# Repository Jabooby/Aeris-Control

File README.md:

# AERISCONTROL
Autonomous sail boat with a multiaxial sail control

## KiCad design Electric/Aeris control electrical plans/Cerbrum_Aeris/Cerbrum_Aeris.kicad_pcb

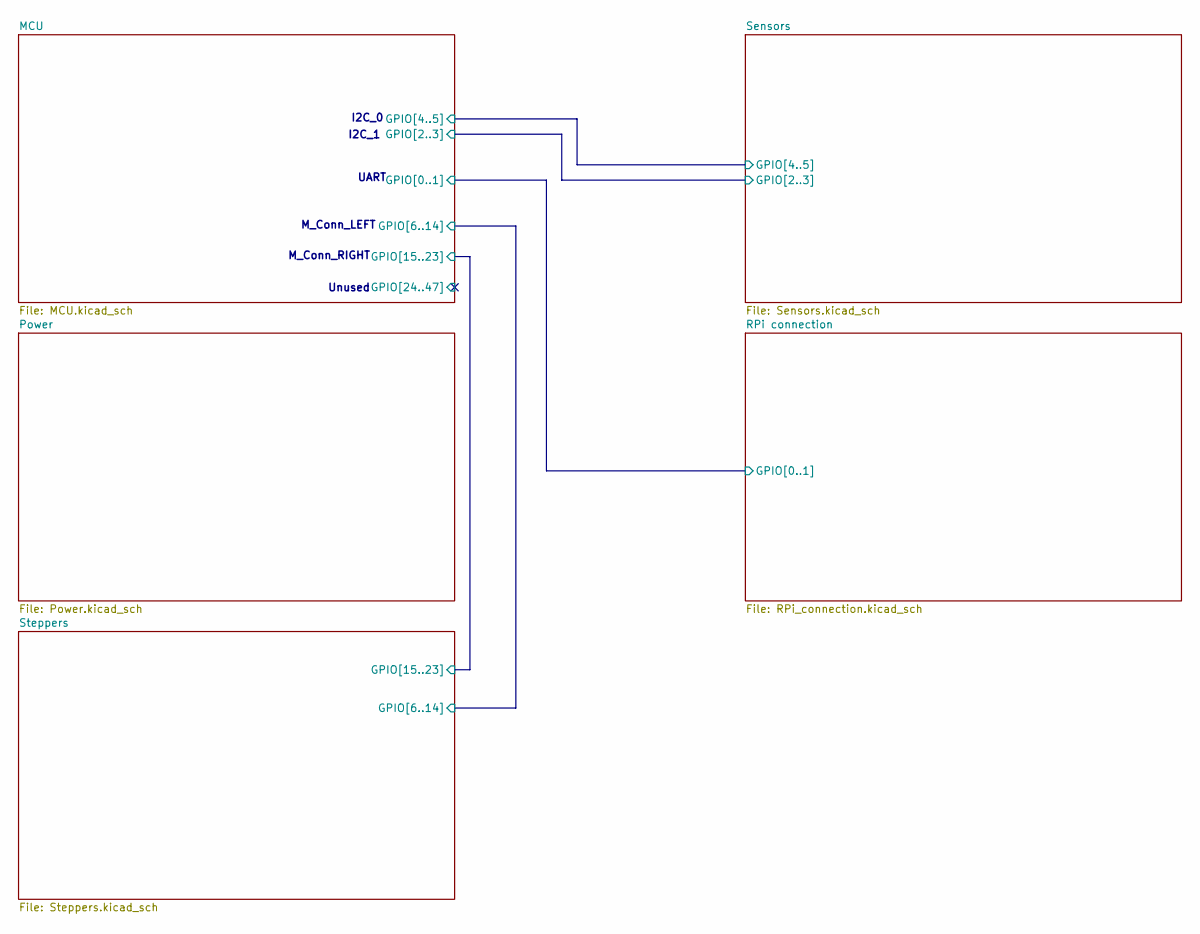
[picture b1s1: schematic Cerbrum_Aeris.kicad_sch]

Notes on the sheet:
Unused
I2C_1
M_Conn_RIGHT
I2C_0
UART
M_Conn_LEFT

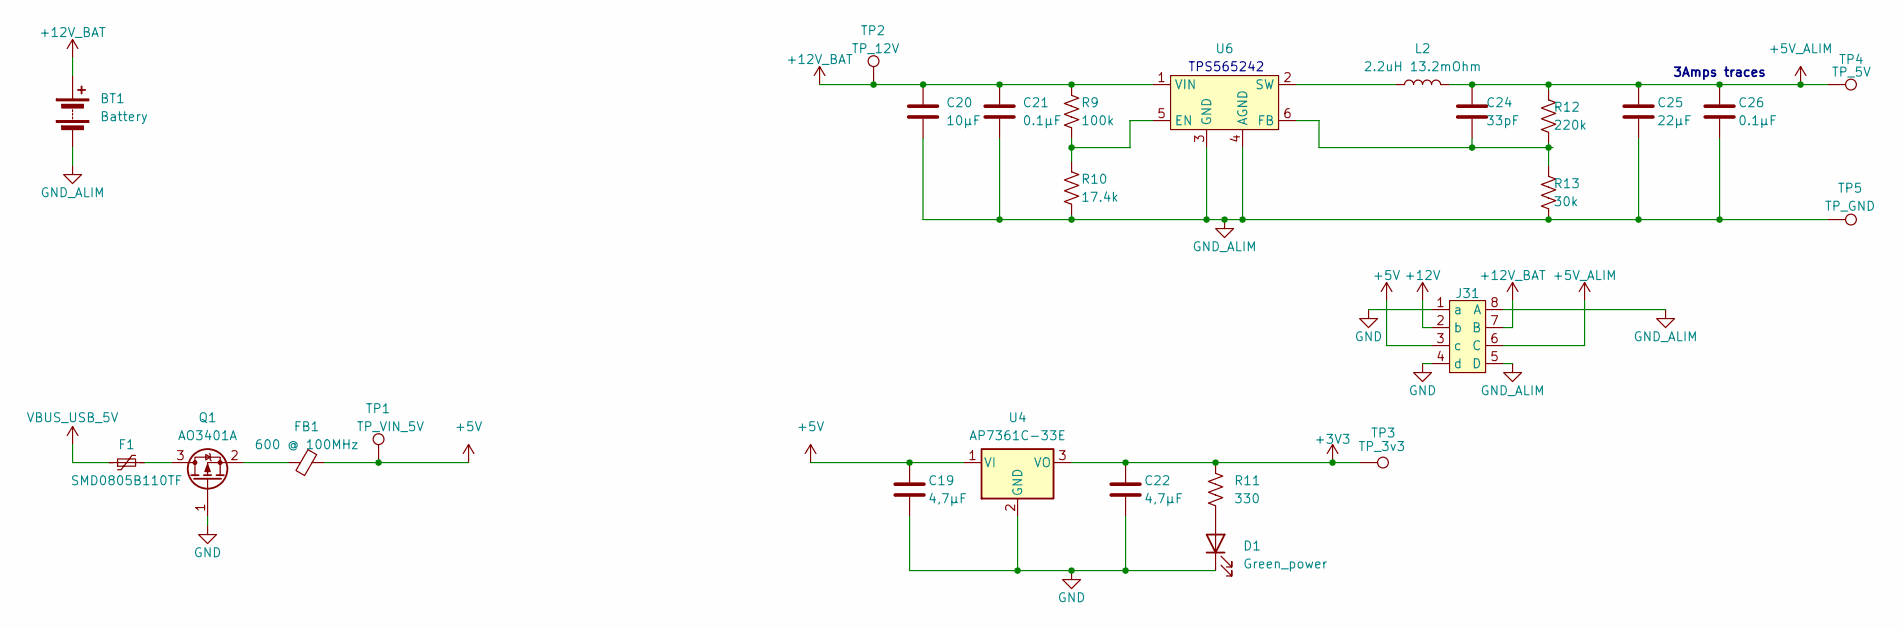
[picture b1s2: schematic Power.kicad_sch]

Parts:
BT1: Battery; TerminalBlock_Altech_AK300-2_P5.00mm
C19, C22: 4,7µF; C_0805_2012Metric_Pad1.18x1.45mm_HandSolder
C20: 10µF; C_0805_2012Metric_Pad1.18x1.45mm_HandSolder
C21, C26: 0.1µF; C_0603_1608Metric_Pad1.08x0.95mm_HandSolder
C24: 33pF; C_0603_1608Metric_Pad1.08x0.95mm_HandSolder
C25: 22µF; C_0805_2012Metric_Pad1.18x1.45mm_HandSolder
D1: Green_power; D_0805_2012Metric
F1: SMD0805B110TF; Fuse_0805_2012Metric
FB1: 600 @ 100MHz; R_0805_2012Metric_Pad1.20x1.40mm_HandSolder
J31: SJ_Stepper_1-5mm
L2: 2.2uH 13.2mOhm; L_TDK_VLP8040
Q1: AO3401A; SOT-23
R9: 100k; R_0603_1608Metric_Pad0.98x0.95mm_HandSolder
R10: 17.4k; R_0603_1608Metric_Pad0.98x0.95mm_HandSolder
R11: 330; R_0603_1608Metric_Pad0.98x0.95mm_HandSolder
R12: 220k; R_0603_1608Metric_Pad0.98x0.95mm_HandSolder
R13: 30k; R_0603_1608Metric_Pad0.98x0.95mm_HandSolder
TP1: TP_VIN_5V; TestPoint_Pad_D1.0mm
TP2: TP_12V; TestPoint_Pad_D1.0mm
TP3: TP_3v3; TestPoint_Pad_D1.0mm
TP4: TP_5V; TestPoint_Pad_D1.0mm
TP5: TP_GND; TestPoint_Pad_1.0x1.0mm
U4: AP7361C-33E; SOT-223-3_TabPin2
U6: SOT-563

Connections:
+3V3: C22.2, R11.1, TP3.1, U4.3 (VO); also elsewhere on the board
+5V: C19.2, FB1.2, J31.3 (c), TP1.1, U4.1 (VI); also elsewhere on the board
+5V_ALIM: C24.1, C25.1, C26.1, J31.6 (C), L2.2, R12.1, TP4.1; also elsewhere on the board
+12V: J31.2 (b); also elsewhere on the board
+12V_BAT: BT1.1 (+), C20.1, C21.1, J31.7 (B), R9.1, TP2.1, U6.1 (VIN); also elsewhere on the board
GND: C19.1, C22.1, D1.1 (K), J31.1 (a), J31.4 (d), Q1.1 (G), U4.2 (GND); also elsewhere on the board
GND_ALIM: BT1.2 (-), C20.2, C21.2, C25.2, C26.2, J31.5 (D), J31.8 (A), R10.2, R13.2, TP5.1, U6.3 (GND), U6.4 (AGND); also elsewhere on the board
unnamed: D1.2 (A), R11.2
unnamed: F1.2, Q1.3 (D)
unnamed: FB1.1, Q1.2 (S)
unnamed: R9.2, R10.1, U6.5 (EN)
unnamed: C24.2, R12.2, R13.1, U6.6 (FB)
unnamed: L2.1, U6.2 (SW)
VBUS_USB_5V: F1.1; also elsewhere on the board

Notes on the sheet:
TPS565242
3Amps traces

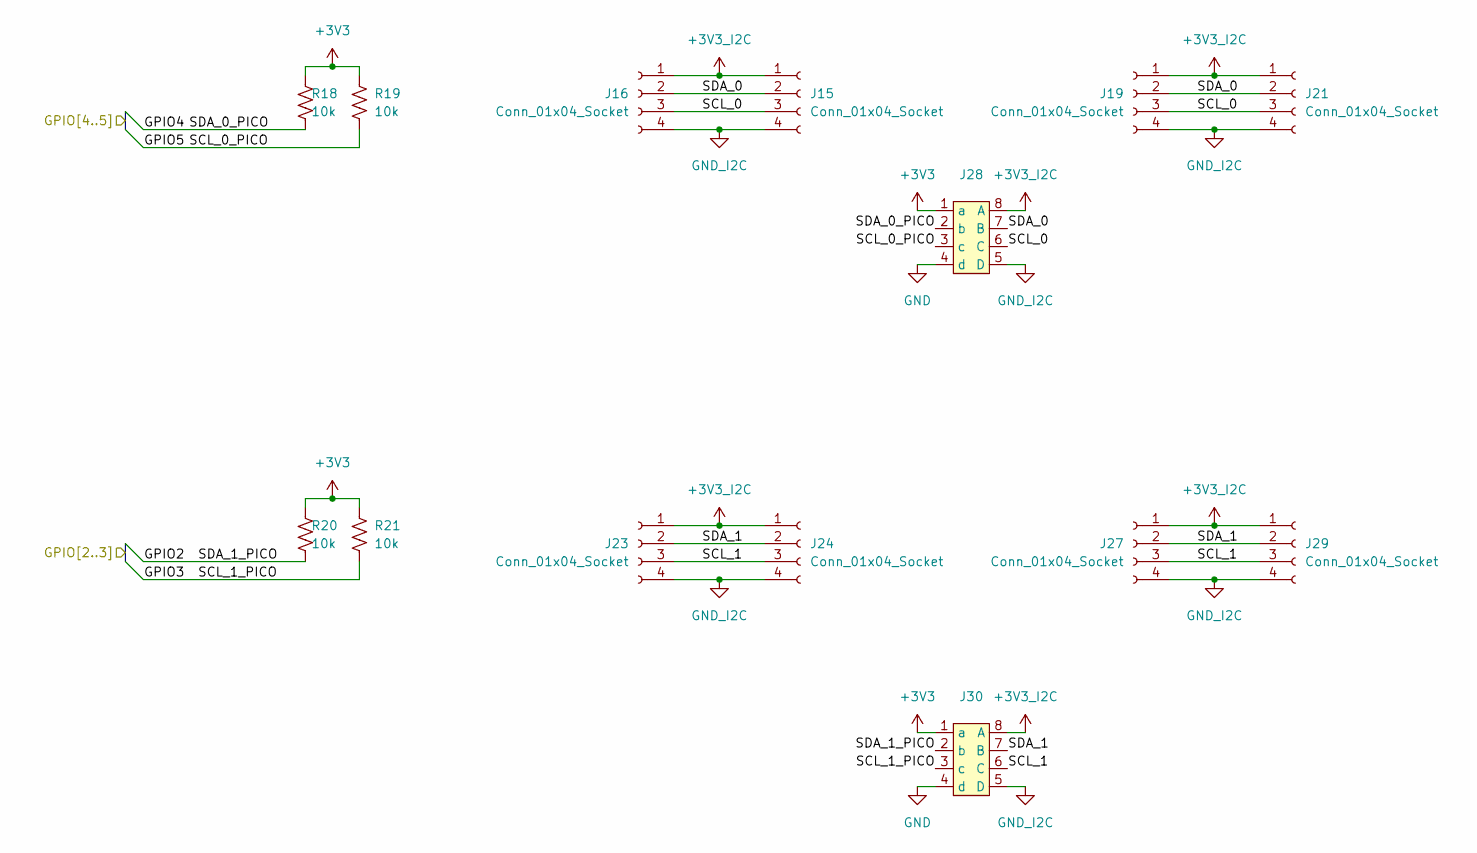
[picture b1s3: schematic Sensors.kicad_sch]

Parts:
J15, J16, J19, J21, J23, J24, J27, J29: Conn_01x04_Socket; PinSocket_1x04_P2.54mm_Vertical
J28, J30: SJ_Stepper_1-5mm
R18, R19, R20, R21: 10k; R_0603_1608Metric

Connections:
+3V3: J28.1 (a), J30.1 (a), R18.1, R19.1, R20.1, R21.1; also elsewhere on the board
+3V3_I2C: J15.1, J16.1, J19.1, J21.1, J23.1, J24.1, J27.1, J28.8 (A), J29.1, J30.8 (A)
/MCU/GPIO2: J30.2 (b), R20.2; also elsewhere on the board
/MCU/GPIO3: J30.3 (c), R21.2; also elsewhere on the board
/MCU/GPIO4: J28.2 (b), R18.2; also elsewhere on the board
/MCU/GPIO5: J28.3 (c), R19.2; also elsewhere on the board
/Sensors/SCL_0: J15.3, J16.3, J19.3, J21.3, J28.6 (C)
/Sensors/SCL_1: J23.3, J24.3, J27.3, J29.3, J30.6 (C)
/Sensors/SDA_0: J15.2, J16.2, J19.2, J21.2, J28.7 (B)
/Sensors/SDA_1: J23.2, J24.2, J27.2, J29.2, J30.7 (B)
GND: J28.4 (d), J30.4 (d); also elsewhere on the board
GND_I2C: J15.4, J16.4, J19.4, J21.4, J23.4, J24.4, J27.4, J28.5 (D), J29.4, J30.5 (D)

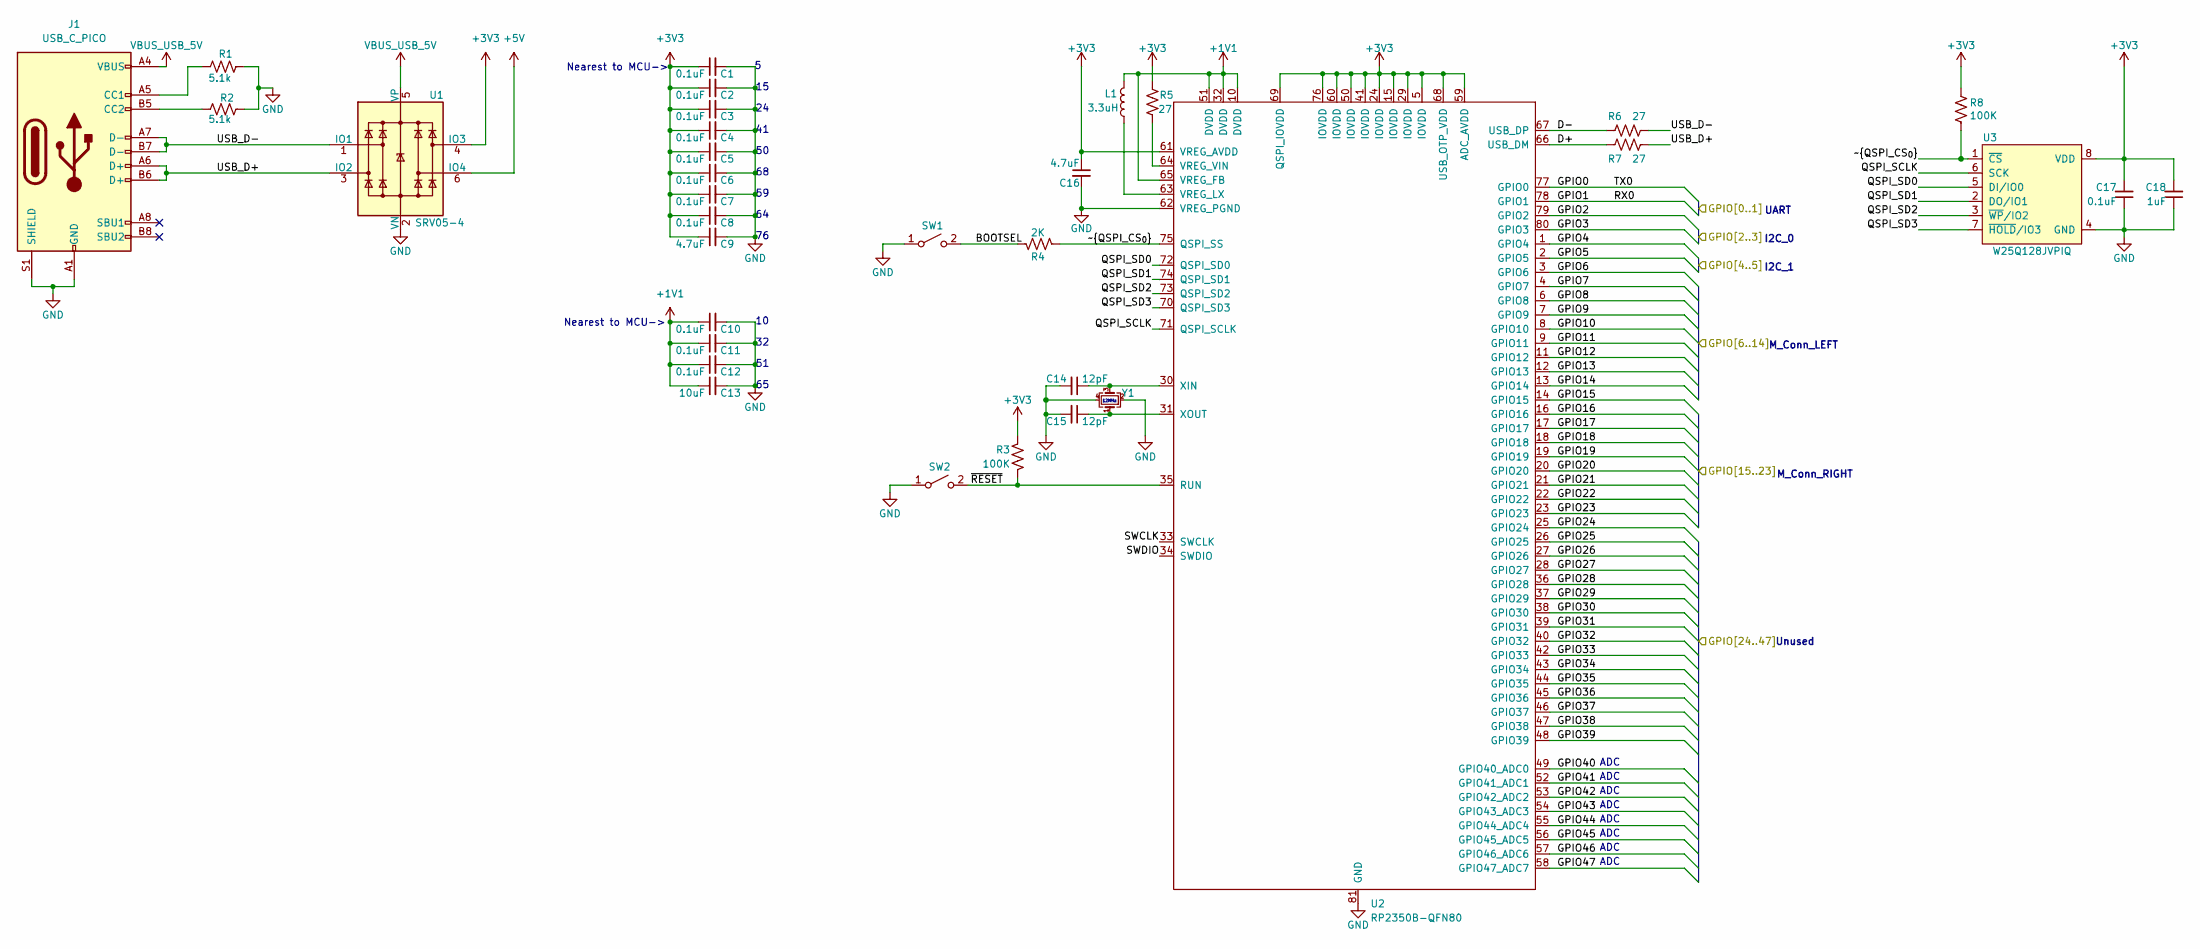
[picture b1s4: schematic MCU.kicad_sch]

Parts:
C1, C2, C3, C4, C5, C6, C7, C8, C10, C11, C12, C17: 0.1uF; C_0603_1608Metric
C9, C16: 4.7uF; C_0603_1608Metric
C13: 10uF; C_0603_1608Metric
C14, C15: 12pF; C_0603_1608Metric
C18: 1uF; C_0603_1608Metric
J1: USB_C_PICO; USB_C_Receptacle_G-Switch_GT-USB-7010ASV
L1: 3.3uH; R_0805_2012Metric
R1, R2: 5.1k; R_0603_1608Metric_Pad0.98x0.95mm_HandSolder
R3, R8: 100K; R_0603_1608Metric
R4: 2K; R_0603_1608Metric
R5, R6, R7: 27; R_0603_1608Metric
SW1: SW_BOOTSEL; SW_SPST_B3U-1000P; LCSC C561514
SW2: SW_RESET; SW_SPST_B3U-1000P; LCSC C561514
U1: SRV05-4; SOT-23-6
U2: RP2350B-QFN80; QFN-80-1EP_10x10mm_P0.4mm_EP3.4x3.4mm_ThermalVias
U3: W25Q128JVPIQ; WSON-8-1EP_6x5mm_P1.27mm_EP3.4x4mm; LCSC C190862
Y1: CM4012M00012001; Crystal_SMD_2520-4Pin_2.5x2.0mm; LCSC C7294611

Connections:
+1V1: C10.1, C11.1, C12.1, C13.1, L1.2, U2.10 (DVDD), U2.32 (DVDD), U2.51 (DVDD), U2.65 (VREG_FB)
+3V3: C1.1, C2.1, C3.1, C4.1, C5.1, C6.1, C7.1, C8.1, C9.1, C16.1, C17.2, C18.2, R3.1, R5.1, R8.2, U1.4 (IO3), U2.5 (IOVDD), U2.15 (IOVDD), U2.24 (IOVDD), U2.29 (IOVDD), U2.41 (IOVDD), U2.50 (IOVDD), U2.59 (ADC_AVDD), U2.60 (IOVDD), U2.61 (VREG_AVDD), U2.68 (USB_OTP_VDD), U2.69 (QSPI_IOVDD), U2.76 (IOVDD), U3.8 (VDD); also elsewhere on the board
+5V: U1.6 (IO4); also elsewhere on the board
/MCU/BOOTSEL: R4.2, SW1.2 (B); also elsewhere on the board
/MCU/D+: R7.2, U2.66 (USB_DM)
/MCU/D-: R6.1, U2.67 (USB_DP)
/MCU/GPIO0: U2.77 (GPIO0); also elsewhere on the board
/MCU/GPIO1: U2.78 (GPIO1); also elsewhere on the board
/MCU/GPIO2: U2.79 (GPIO2); also elsewhere on the board
/MCU/GPIO3: U2.80 (GPIO3); also elsewhere on the board
/MCU/GPIO4: U2.1 (GPIO4); also elsewhere on the board
/MCU/GPIO5: U2.2 (GPIO5); also elsewhere on the board
/MCU/GPIO6: U2.3 (GPIO6); also elsewhere on the board
/MCU/GPIO7: U2.4 (GPIO7); also elsewhere on the board
/MCU/GPIO8: U2.6 (GPIO8); also elsewhere on the board
/MCU/GPIO9: U2.7 (GPIO9); also elsewhere on the board
/MCU/GPIO10: U2.8 (GPIO10); also elsewhere on the board
/MCU/GPIO11: U2.9 (GPIO11); also elsewhere on the board
/MCU/GPIO12: U2.11 (GPIO12); also elsewhere on the board
/MCU/GPIO13: U2.12 (GPIO13); also elsewhere on the board
/MCU/GPIO14: U2.13 (GPIO14); also elsewhere on the board
/MCU/GPIO15: U2.14 (GPIO15); also elsewhere on the board
/MCU/GPIO16: U2.16 (GPIO16); also elsewhere on the board
/MCU/GPIO17: U2.17 (GPIO17); also elsewhere on the board
/MCU/GPIO18: U2.18 (GPIO18); also elsewhere on the board
/MCU/GPIO19: U2.19 (GPIO19); also elsewhere on the board
/MCU/GPIO20: U2.20 (GPIO20); also elsewhere on the board
/MCU/GPIO21: U2.21 (GPIO21); also elsewhere on the board
/MCU/GPIO22: U2.22 (GPIO22); also elsewhere on the board
/MCU/GPIO23: U2.23 (GPIO23); also elsewhere on the board
/MCU/GPIO24: U2.25 (GPIO24)
/MCU/GPIO25: U2.26 (GPIO25)
/MCU/GPIO26: U2.27 (GPIO26)
/MCU/GPIO27: U2.28 (GPIO27)
/MCU/GPIO28: U2.36 (GPIO28)
/MCU/GPIO29: U2.37 (GPIO29)
/MCU/GPIO30: U2.38 (GPIO30)
/MCU/GPIO31: U2.39 (GPIO31)
/MCU/GPIO32: U2.40 (GPIO32)
/MCU/GPIO33: U2.42 (GPIO33)
/MCU/GPIO34: U2.43 (GPIO34)
/MCU/GPIO35: U2.44 (GPIO35)
/MCU/GPIO36: U2.45 (GPIO36)
/MCU/GPIO37: U2.46 (GPIO37)
/MCU/GPIO38: U2.47 (GPIO38)
/MCU/GPIO39: U2.48 (GPIO39)
/MCU/GPIO40: U2.49 (GPIO40_ADC0)
/MCU/GPIO41: U2.52 (GPIO41_ADC1)
/MCU/GPIO42: U2.53 (GPIO42_ADC2)
/MCU/GPIO43: U2.54 (GPIO43_ADC3)
/MCU/GPIO44: U2.55 (GPIO44_ADC4)
/MCU/GPIO45: U2.56 (GPIO45_ADC5)
/MCU/GPIO46: U2.57 (GPIO46_ADC6)
/MCU/GPIO47: U2.58 (GPIO47_ADC7)
/MCU/QSPI_SCLK: U2.71 (QSPI_SCLK), U3.6 (SCK)
/MCU/QSPI_SD0: U2.72 (QSPI_SD0), U3.5 (DI/IO0)
/MCU/QSPI_SD1: U2.74 (QSPI_SD1), U3.2 (DO/IO1)
/MCU/QSPI_SD2: U2.73 (QSPI_SD2), U3.3 (~WP/IO2)
/MCU/QSPI_SD3: U2.70 (QSPI_SD3), U3.7 (~HOLD/IO3)
/MCU/SWCLK: U2.33 (SWCLK)
/MCU/SWDIO: U2.34 (SWDIO)
/MCU/USB_D+: J1.A6 (D+), J1.B6 (D+), R7.1, U1.3 (IO2)
/MCU/USB_D-: J1.A7 (D-), J1.B7 (D-), R6.2, U1.1 (IO1)
/MCU/~QSPI_CS_{0}: R4.1, R8.1, U2.75 (QSPI_SS), U3.1 (~CS)
/MCU/~RESET: R3.2, SW2.2 (B), U2.35 (RUN); also elsewhere on the board
GND: C1.2, C2.2, C3.2, C4.2, C5.2, C6.2, C7.2, C8.2, C9.2, C10.2, C11.2, C12.2, C13.2, C14.2, C15.2, C16.2, C17.1, C18.1, J1.A1 (GND), J1.A12 (GND), J1.B1 (GND), J1.B12 (GND), J1.S1 (SHIELD), R1.2, R2.2, SW1.1 (A), SW2.1 (A), U1.2 (VN), U2.62 (VREG_PGND), U2.81 (GND), U3.4 (GND), U3.9 (GND), Y1.2, Y1.4; also elsewhere on the board
unnamed: J1.A5 (CC1), R1.1
unnamed: J1.B5 (CC2), R2.1
unnamed: L1.1, U2.63 (VREG_LX)
unnamed: R5.2, U2.64 (VREG_VIN)
unnamed: C14.1, U2.30 (XIN), Y1.3
unnamed: C15.1, U2.31 (XOUT), Y1.1
VBUS_USB_5V: J1.A4 (VBUS), J1.A9 (VBUS), J1.B4 (VBUS), J1.B9 (VBUS), U1.5 (VP); also elsewhere on the board

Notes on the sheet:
Nearest to MCU->
M_Conn_LEFT
ADC
Unused
I2C_0
M_Conn_RIGHT
12MHz
I2C_1
UART

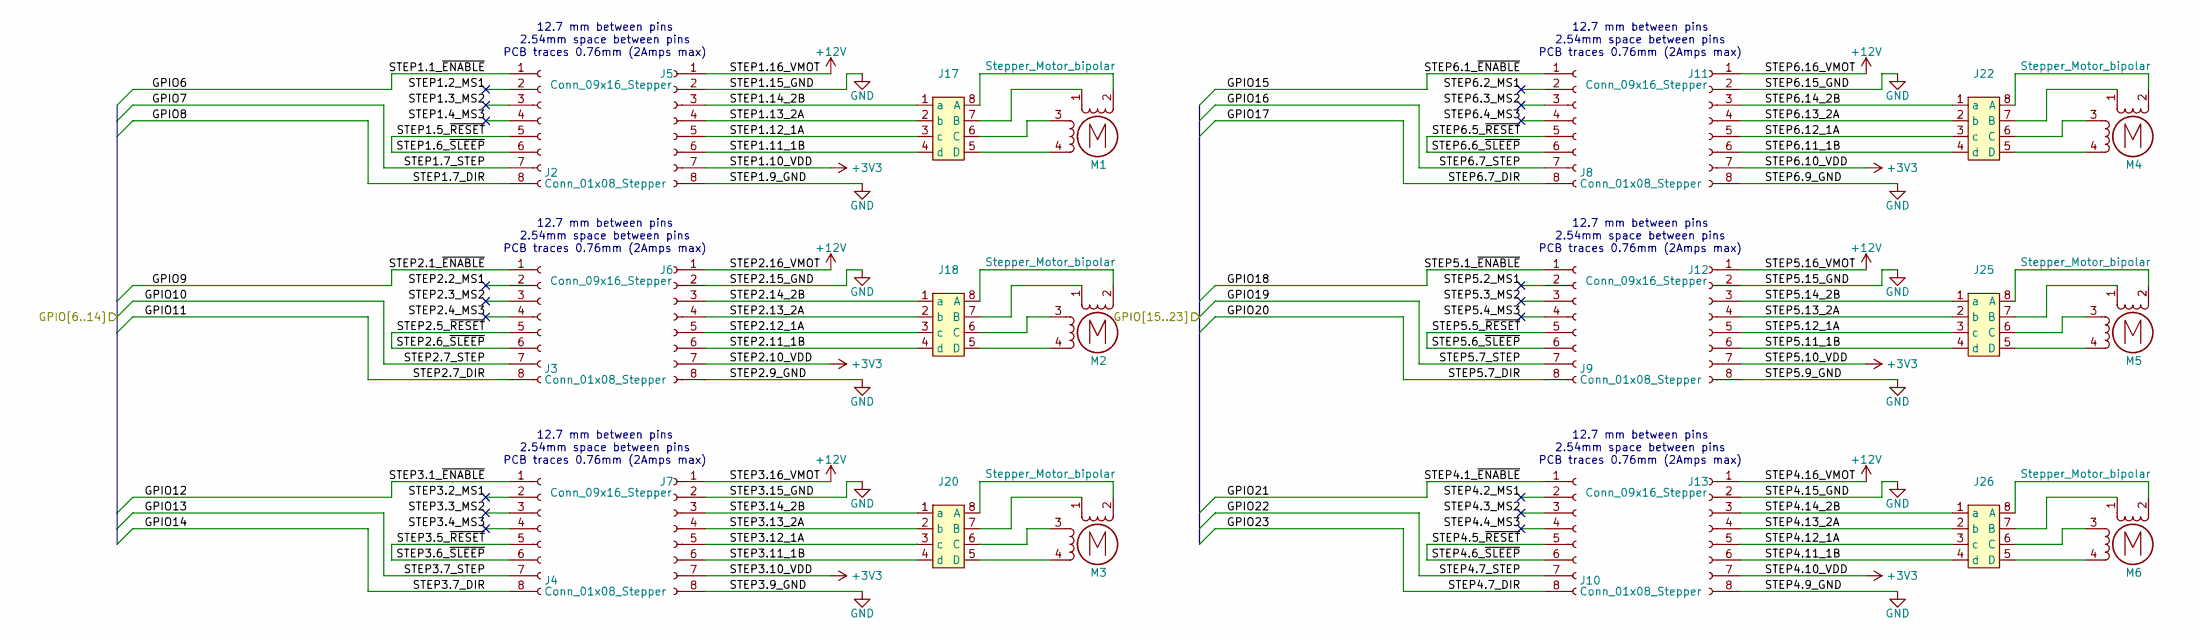
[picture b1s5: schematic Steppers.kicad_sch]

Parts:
J2, J3, J4, J8, J9, J10: Conn_01x08_Stepper; PinSocket_1x08_P2.54mm_Vertical_SMD_Pin1Left
J5, J6, J7, J11, J12, J13: Conn_09x16_Stepper; PinSocket_1x08_P2.54mm_Vertical_SMD_Pin1Left
J17, J18, J20, J22, J25, J26: SJ_Stepper_1-5mm
M1, M2, M3, M4, M5, M6: Stepper_Motor_bipolar; PinSocket_1x04_P2.54mm_Vertical

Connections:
+3V3: J5.7, J6.7, J7.7, J11.7, J12.7, J13.7; also elsewhere on the board
+12V: J5.1, J6.1, J7.1, J11.1, J12.1, J13.1; also elsewhere on the board
/MCU/GPIO6: J2.1; also elsewhere on the board
/MCU/GPIO7: J2.7; also elsewhere on the board
/MCU/GPIO8: J2.8; also elsewhere on the board
/MCU/GPIO9: J3.1; also elsewhere on the board
/MCU/GPIO10: J3.7; also elsewhere on the board
/MCU/GPIO11: J3.8; also elsewhere on the board
/MCU/GPIO12: J4.1; also elsewhere on the board
/MCU/GPIO13: J4.7; also elsewhere on the board
/MCU/GPIO14: J4.8; also elsewhere on the board
/MCU/GPIO15: J8.1; also elsewhere on the board
/MCU/GPIO16: J8.7; also elsewhere on the board
/MCU/GPIO17: J8.8; also elsewhere on the board
/MCU/GPIO18: J9.1; also elsewhere on the board
/MCU/GPIO19: J9.7; also elsewhere on the board
/MCU/GPIO20: J9.8; also elsewhere on the board
/MCU/GPIO21: J10.1; also elsewhere on the board
/MCU/GPIO22: J10.7; also elsewhere on the board
/MCU/GPIO23: J10.8; also elsewhere on the board
/Steppers/STEP1.2_MS1: J2.2
/Steppers/STEP1.3_MS2: J2.3
/Steppers/STEP1.4_MS3: J2.4
/Steppers/STEP1.5_~RESET: J2.5, J2.6
/Steppers/STEP1.11_1B: J5.6, J17.4 (d)
/Steppers/STEP1.12_1A: J5.5, J17.3 (c)
/Steppers/STEP1.13_2A: J5.4, J17.2 (b)
/Steppers/STEP1.14_2B: J5.3, J17.1 (a)
/Steppers/STEP2.2_MS1: J3.2
/Steppers/STEP2.3_MS2: J3.3
/Steppers/STEP2.4_MS3: J3.4
/Steppers/STEP2.5_~RESET: J3.5, J3.6
/Steppers/STEP2.11_1B: J6.6, J18.4 (d)
/Steppers/STEP2.12_1A: J6.5, J18.3 (c)
/Steppers/STEP2.13_2A: J6.4, J18.2 (b)
/Steppers/STEP2.14_2B: J6.3, J18.1 (a)
/Steppers/STEP3.2_MS1: J4.2
/Steppers/STEP3.3_MS2: J4.3
/Steppers/STEP3.4_MS3: J4.4
/Steppers/STEP3.5_~RESET: J4.5, J4.6
/Steppers/STEP3.11_1B: J7.6, J20.4 (d)
/Steppers/STEP3.12_1A: J7.5, J20.3 (c)
/Steppers/STEP3.13_2A: J7.4, J20.2 (b)
/Steppers/STEP3.14_2B: J7.3, J20.1 (a)
/Steppers/STEP4.2_MS1: J10.2
/Steppers/STEP4.3_MS2: J10.3
/Steppers/STEP4.4_MS3: J10.4
/Steppers/STEP4.5_~RESET: J10.5, J10.6
/Steppers/STEP4.11_1B: J13.6, J26.4 (d)
/Steppers/STEP4.12_1A: J13.5, J26.3 (c)
/Steppers/STEP4.13_2A: J13.4, J26.2 (b)
/Steppers/STEP4.14_2B: J13.3, J26.1 (a)
/Steppers/STEP5.2_MS1: J9.2
/Steppers/STEP5.3_MS2: J9.3
/Steppers/STEP5.4_MS3: J9.4
/Steppers/STEP5.5_~RESET: J9.5, J9.6
/Steppers/STEP5.11_1B: J12.6, J25.4 (d)
/Steppers/STEP5.12_1A: J12.5, J25.3 (c)
/Steppers/STEP5.13_2A: J12.4, J25.2 (b)
/Steppers/STEP5.14_2B: J12.3, J25.1 (a)
/Steppers/STEP6.2_MS1: J8.2
/Steppers/STEP6.3_MS2: J8.3
/Steppers/STEP6.4_MS3: J8.4
/Steppers/STEP6.5_~RESET: J8.5, J8.6
/Steppers/STEP6.11_1B: J11.6, J22.4 (d)
/Steppers/STEP6.12_1A: J11.5, J22.3 (c)
/Steppers/STEP6.13_2A: J11.4, J22.2 (b)
/Steppers/STEP6.14_2B: J11.3, J22.1 (a)
GND: J5.2, J5.8, J6.2, J6.8, J7.2, J7.8, J11.2, J11.8, J12.2, J12.8, J13.2, J13.8; also elsewhere on the board
unnamed: J17.8 (A), M1.2 (-)
unnamed: J17.7 (B), M1.1
unnamed: J17.6 (C), M1.3
unnamed: J17.5 (D), M1.4
unnamed: J18.8 (A), M2.2 (-)
unnamed: J18.7 (B), M2.1
unnamed: J18.6 (C), M2.3
unnamed: J18.5 (D), M2.4
unnamed: J20.8 (A), M3.2 (-)
unnamed: J20.7 (B), M3.1
unnamed: J20.6 (C), M3.3
unnamed: J20.5 (D), M3.4
unnamed: J22.8 (A), M4.2 (-)
unnamed: J22.7 (B), M4.1
unnamed: J22.6 (C), M4.3
unnamed: J22.5 (D), M4.4
unnamed: J25.8 (A), M5.2 (-)
unnamed: J25.7 (B), M5.1
unnamed: J25.6 (C), M5.3
unnamed: J25.5 (D), M5.4
unnamed: J26.8 (A), M6.2 (-)
unnamed: J26.7 (B), M6.1
unnamed: J26.6 (C), M6.3
unnamed: J26.5 (D), M6.4

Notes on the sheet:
12.7 mm between pins 2.54mm space between pins PCB traces 0.76mm (2Amps max)

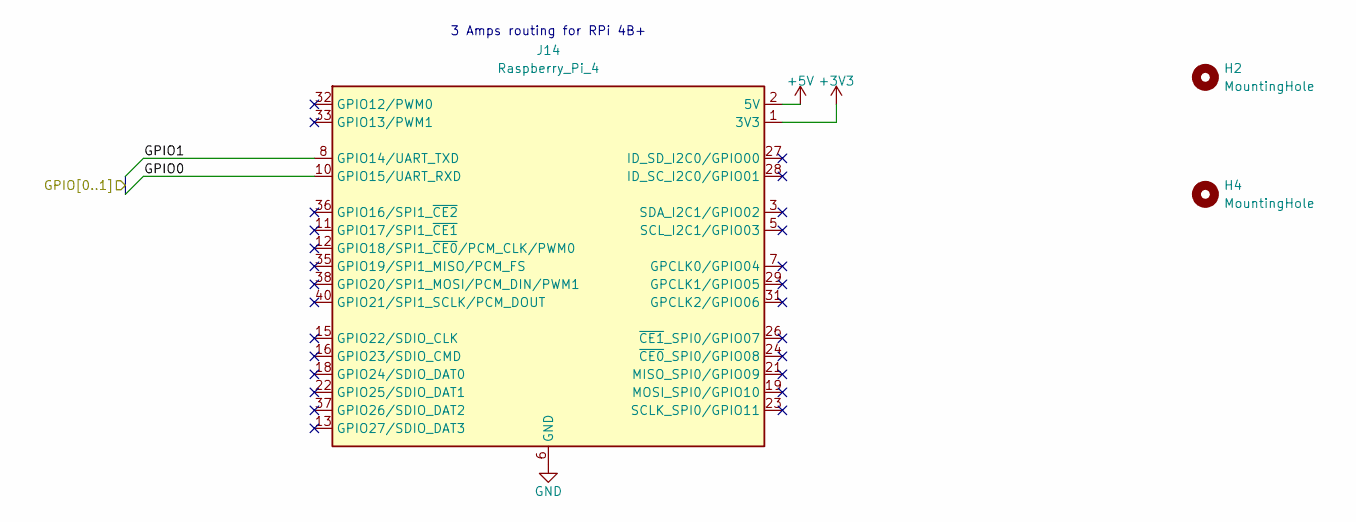
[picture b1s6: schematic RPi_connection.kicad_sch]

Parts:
H2, H4: MountingHole; MountingHole_3.5mm
J14: Raspberry_Pi_4; PinSocket_2x20_P2.54mm_Vertical_SMD

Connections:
+3V3: J14.1 (3V3), J14.17 (3V3); also elsewhere on the board
+5V: J14.2 (5V), J14.4 (5V); also elsewhere on the board
/MCU/GPIO0: J14.10 (GPIO15/UART_RXD); also elsewhere on the board
/MCU/GPIO1: J14.8 (GPIO14/UART_TXD); also elsewhere on the board
GND: J14.6 (GND), J14.9 (GND), J14.14 (GND), J14.20 (GND), J14.25 (GND), J14.30 (GND), J14.34 (GND), J14.39 (GND); also elsewhere on the board

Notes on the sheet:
3 Amps routing for RPi 4B+

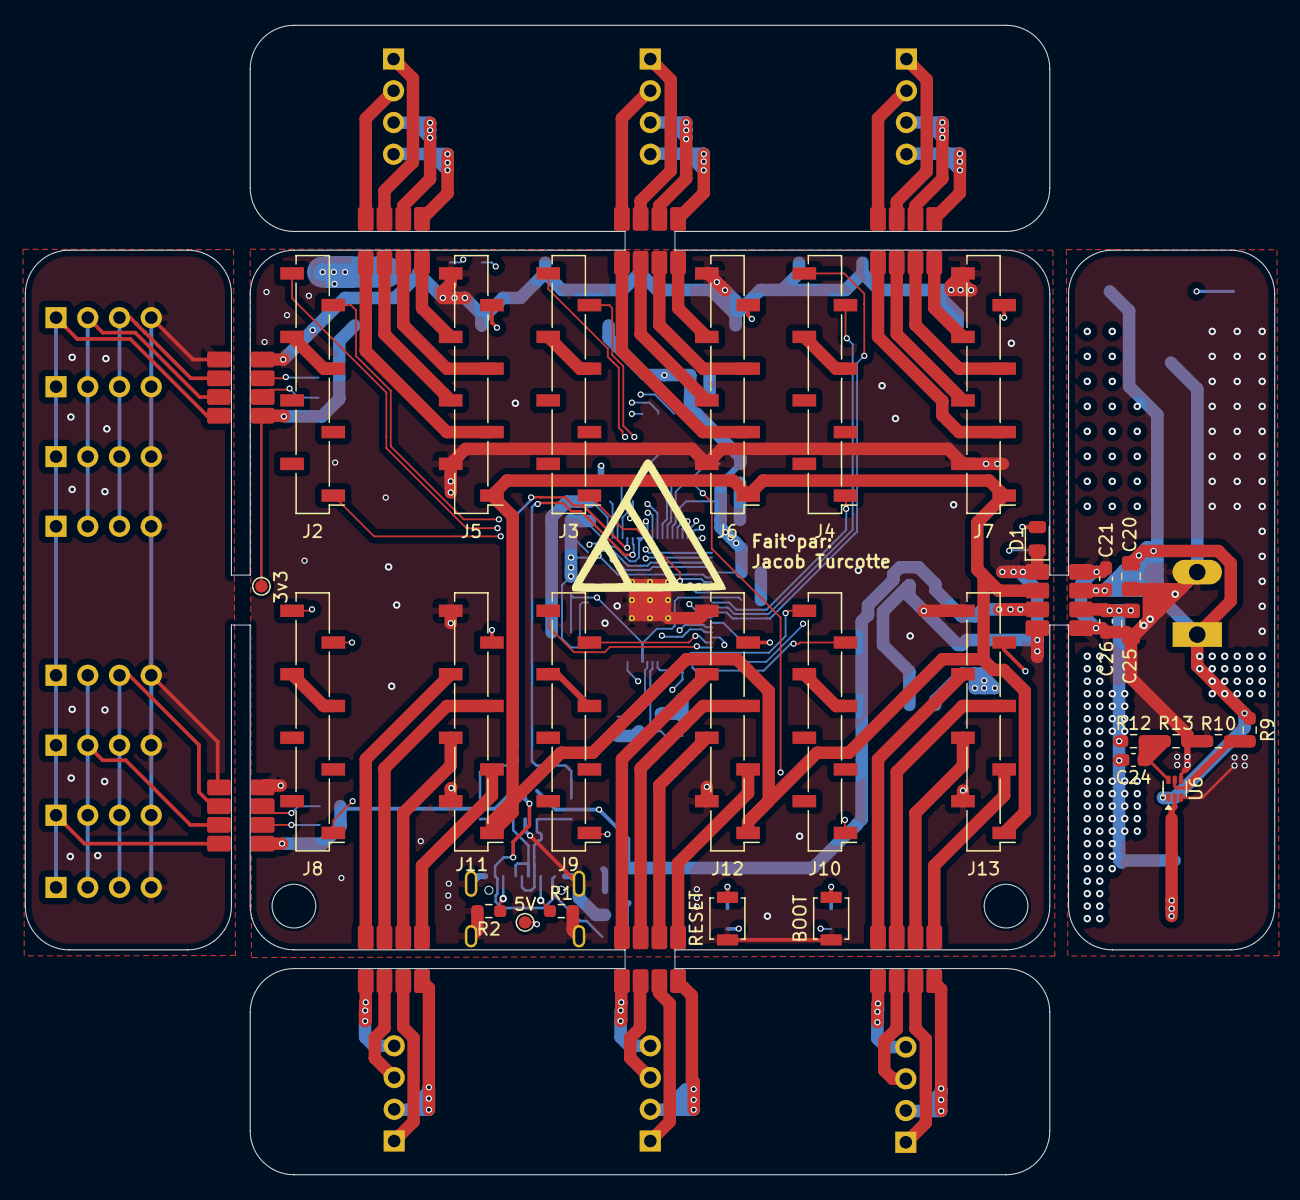
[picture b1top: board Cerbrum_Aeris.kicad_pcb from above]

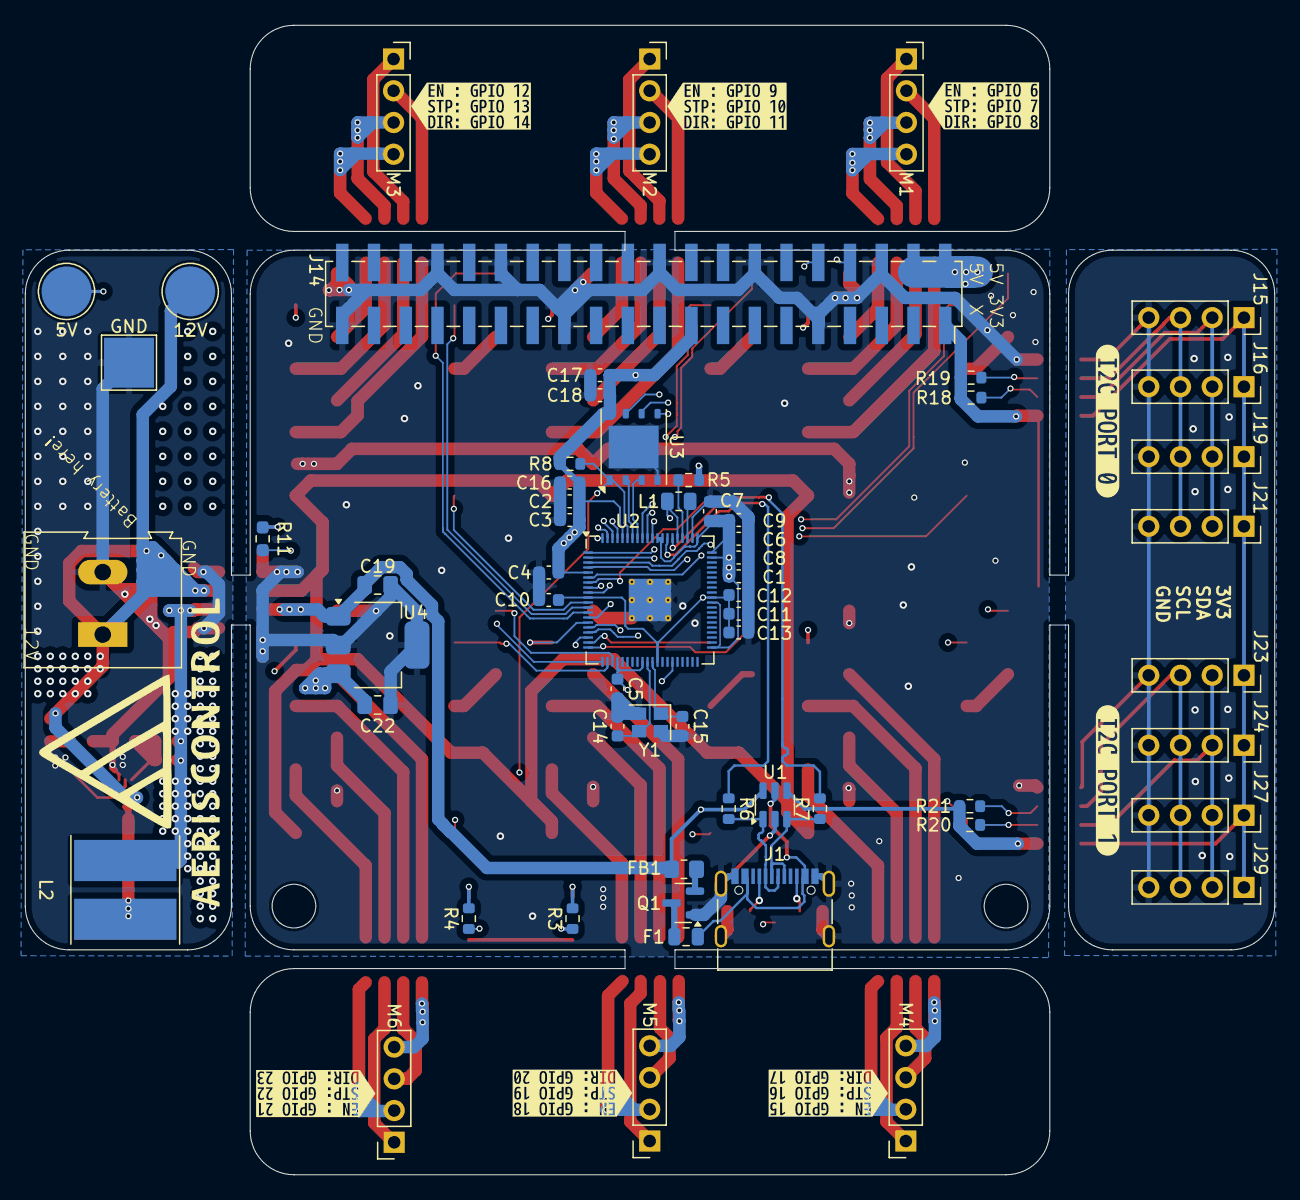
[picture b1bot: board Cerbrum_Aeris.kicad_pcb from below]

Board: 4 copper layers, 100.0 x 92.0 mm, 109 parts (69 on the bottom side), 117 nets.

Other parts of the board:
3v3: TP_3v3; TestPoint_Pad_D1.0mm
5V: TP_VIN_5V; TestPoint_Pad_D1.0mm
5V#2: TP_5V; TestPoint_Pad_D4.0mm
12V: TP_12V; TestPoint_Pad_D4.0mm
BOOT: SW_BOOTSEL; SW_SPST_B3U-1000P
GND: TP_GND; TestPoint_Pad_4.0x4.0mm
RESET: SW_RESET; SW_SPST_B3U-1000P
kibuzzard-67CE33A5: G***; kibuzzard-67CE33A5
kibuzzard-67CE34A5: G***; kibuzzard-67CE34A5
kibuzzard-67CE320A: G***; kibuzzard-67CE320A
kibuzzard-67CE323D: G***; kibuzzard-67CE323D
kibuzzard-67CE3450: G***; kibuzzard-67CE3450
kibuzzard-67CE3465: G***; kibuzzard-67CE3465
kibuzzard-67CE3487: G***; kibuzzard-67CE3487
kibuzzard-67CE3498: G***; kibuzzard-67CE3498

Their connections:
+3V3: 3v3.1; also elsewhere on the board
+5V: 5V.1; also elsewhere on the board
+5V_ALIM: 5V#2.1; also elsewhere on the board
+12V_BAT: 12V.1; also elsewhere on the board
/MCU/BOOTSEL: BOOT.2 (B); also elsewhere on the board
/MCU/~RESET: RESET.2 (B); also elsewhere on the board
GND: BOOT.1 (A), RESET.1 (A); also elsewhere on the board
GND_ALIM: GND.1; also elsewhere on the board

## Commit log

2025-01-29 transfert
2025-01-29 push élec presque terminé
2025-01-29 Parts/Assemblages
2025-01-29 Manette Avec JSON et Bluetooth
2025-02-05 Push motor code
2025-02-05 push handler
2025-02-05 Push, class optimization
2025-02-05 push fix SM
2025-02-05 push code for sensor AS5600 and updates to BMI160
2025-02-05 upload 3D
2025-02-05 added go to position function
2025-02-06 push test
    je vais faire un répertoire /lib bientot que on aura juste à copy paste dans le pico plus tard
2025-02-11 push BMI160, UART and BMI160
2025-02-14 IMU read
2025-02-19 Add files via upload
    IMU fonctionnel
2025-02-19 added position evaluation
2025-02-20 rotations work, position bad
2025-02-20 json for angles
2025-02-20 json added
2025-02-23 Push schéma électrique + pdf
2025-02-23 Push PNG and PDF for stepper motor class
2025-02-25 push code manuel
2025-03-01 Mega push elect
2025-03-04 push éelectrique pcb
2025-03-12 push pcb
2025-03-26 Added wind measurement code
2025-03-26 Class created for windvane and anemometer
    The code is not tested
2025-04-01 push kicad erreurs
2025-04-02 push cleaned up code
2025-04-02 Mech
2025-04-02 pico push
2025-04-02 Wind measurement update
2025-04-02 mech assemblage principale
2025-04-02 Bonnes pin pour le i2c avec le pico à Brampton
2025-04-02 boat
2025-04-05 pid code for orientation, needs to be tested and configured
2025-04-09 new handler for imu
2025-04-09 pids
2025-04-09 Code pour la windvane pas mal finit, cde pour anemometer in progress
2025-04-09 Wind speed code working but needs revision
2025-04-09 Audrey po capable dutiliser git
2025-04-10 audrey
2025-04-10 push clean up nodered
2025-04-13 push
2025-04-13 Update UI
